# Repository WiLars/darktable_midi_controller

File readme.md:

# Midi controller for darktable

- 3D printed housing
  -  stp and stl files available  
- individually illuminated buttons depending on state of the controller using WS2812 RGB LEDs
- arduino compatible pro micro µc
  - extended input channels with 74HC165 shifht registers
  - cherry type mechanical keys
    - 8 top row for mode selction
    - 8 in bottom row for functions
  - 4 alps rotary encoders with button functions
  - powered and connected via usb
- PCB files in KiCad available
- control of darktable via midi protcol
  - fully customizable inside of darktable

## materials
| Part | amount | comment|
| -------- | ------- | ------ |
| PCB | 1 | Kicad files in this repo|
| frontcover | 1 | 3D print|
| backcover | 1 | 3D print|
| LED holder | 1 | 3D print|
| buffer | 7 | 3D print (TPU)|
| encoder knobs | 4 | 3D print|
| keycaps | 16 | 3D print|
| M3x10 screw | 7| |
| micro USB cable| 1 | |
| pro micro atmega32 | 1| arduino compatible cheap MCU|
| 74HC165 | 2|  shift registers|
| cherry type switches | 16 | accordig to taste|
| capacitor 100 nF | 2 | |
| capacitor 1 µF | 2 | or something similar |
| rotary encoder Alps EC12 | 4 | with click|
| pullup resistor | 16 | high resistance recommended > 10k Ohm |
| WS2812 RGB LED | 16 | I used a self adhesive LED strip with 60 LED/m, that way, two can be chained without soldering |
| double tape | some |  to stick the LED holder onto the PCB|
| wire | some | to connect LED strips |

## assembly
- solder al compenents to PCB
- LEDs: this is a little awkward, spacing of LEDs and switches didn't fit and I could't source any reasonably priced THT RGB LEDs
  - two LEDs from the strip are glued to the holder, position is indicated by notches
  - individual strips need to be connected with wire (3 contacts each)
  - LED holder can be glued onto the PCB with some double tape
  - then both strips (top and bottom can be connected to the PCB

- add USB cable
- add TPU buffers to the backcover
- add the case and screws
- knobs and keycaps
- flash arduino SW

## usage
*The controller must be connected during start of darktable, it can only be detected during start!*
after every start, darktable needs to notice that midi CCs are working in relative mode (default is absolute). This can be done by rotating one of the encoders left.

If darktable is running in absolute encoding, input can be reset with ctrl+alt*shift+I then again try to rotate an encoder left.

keymappsings can be imported into darktable: settings -> shortcuts -> import
 => use file *darktable_shortcut_mapping_export*

 With current arduino SW the top row of switches selects the modes, bottom row of buttons and rotary encoders can be assigned to darktable functions

 ## issues
 - darktable does not distinguish for very low "notes" for midi, therefore some buttons cannot be assigned
 - keymapping is not very complete

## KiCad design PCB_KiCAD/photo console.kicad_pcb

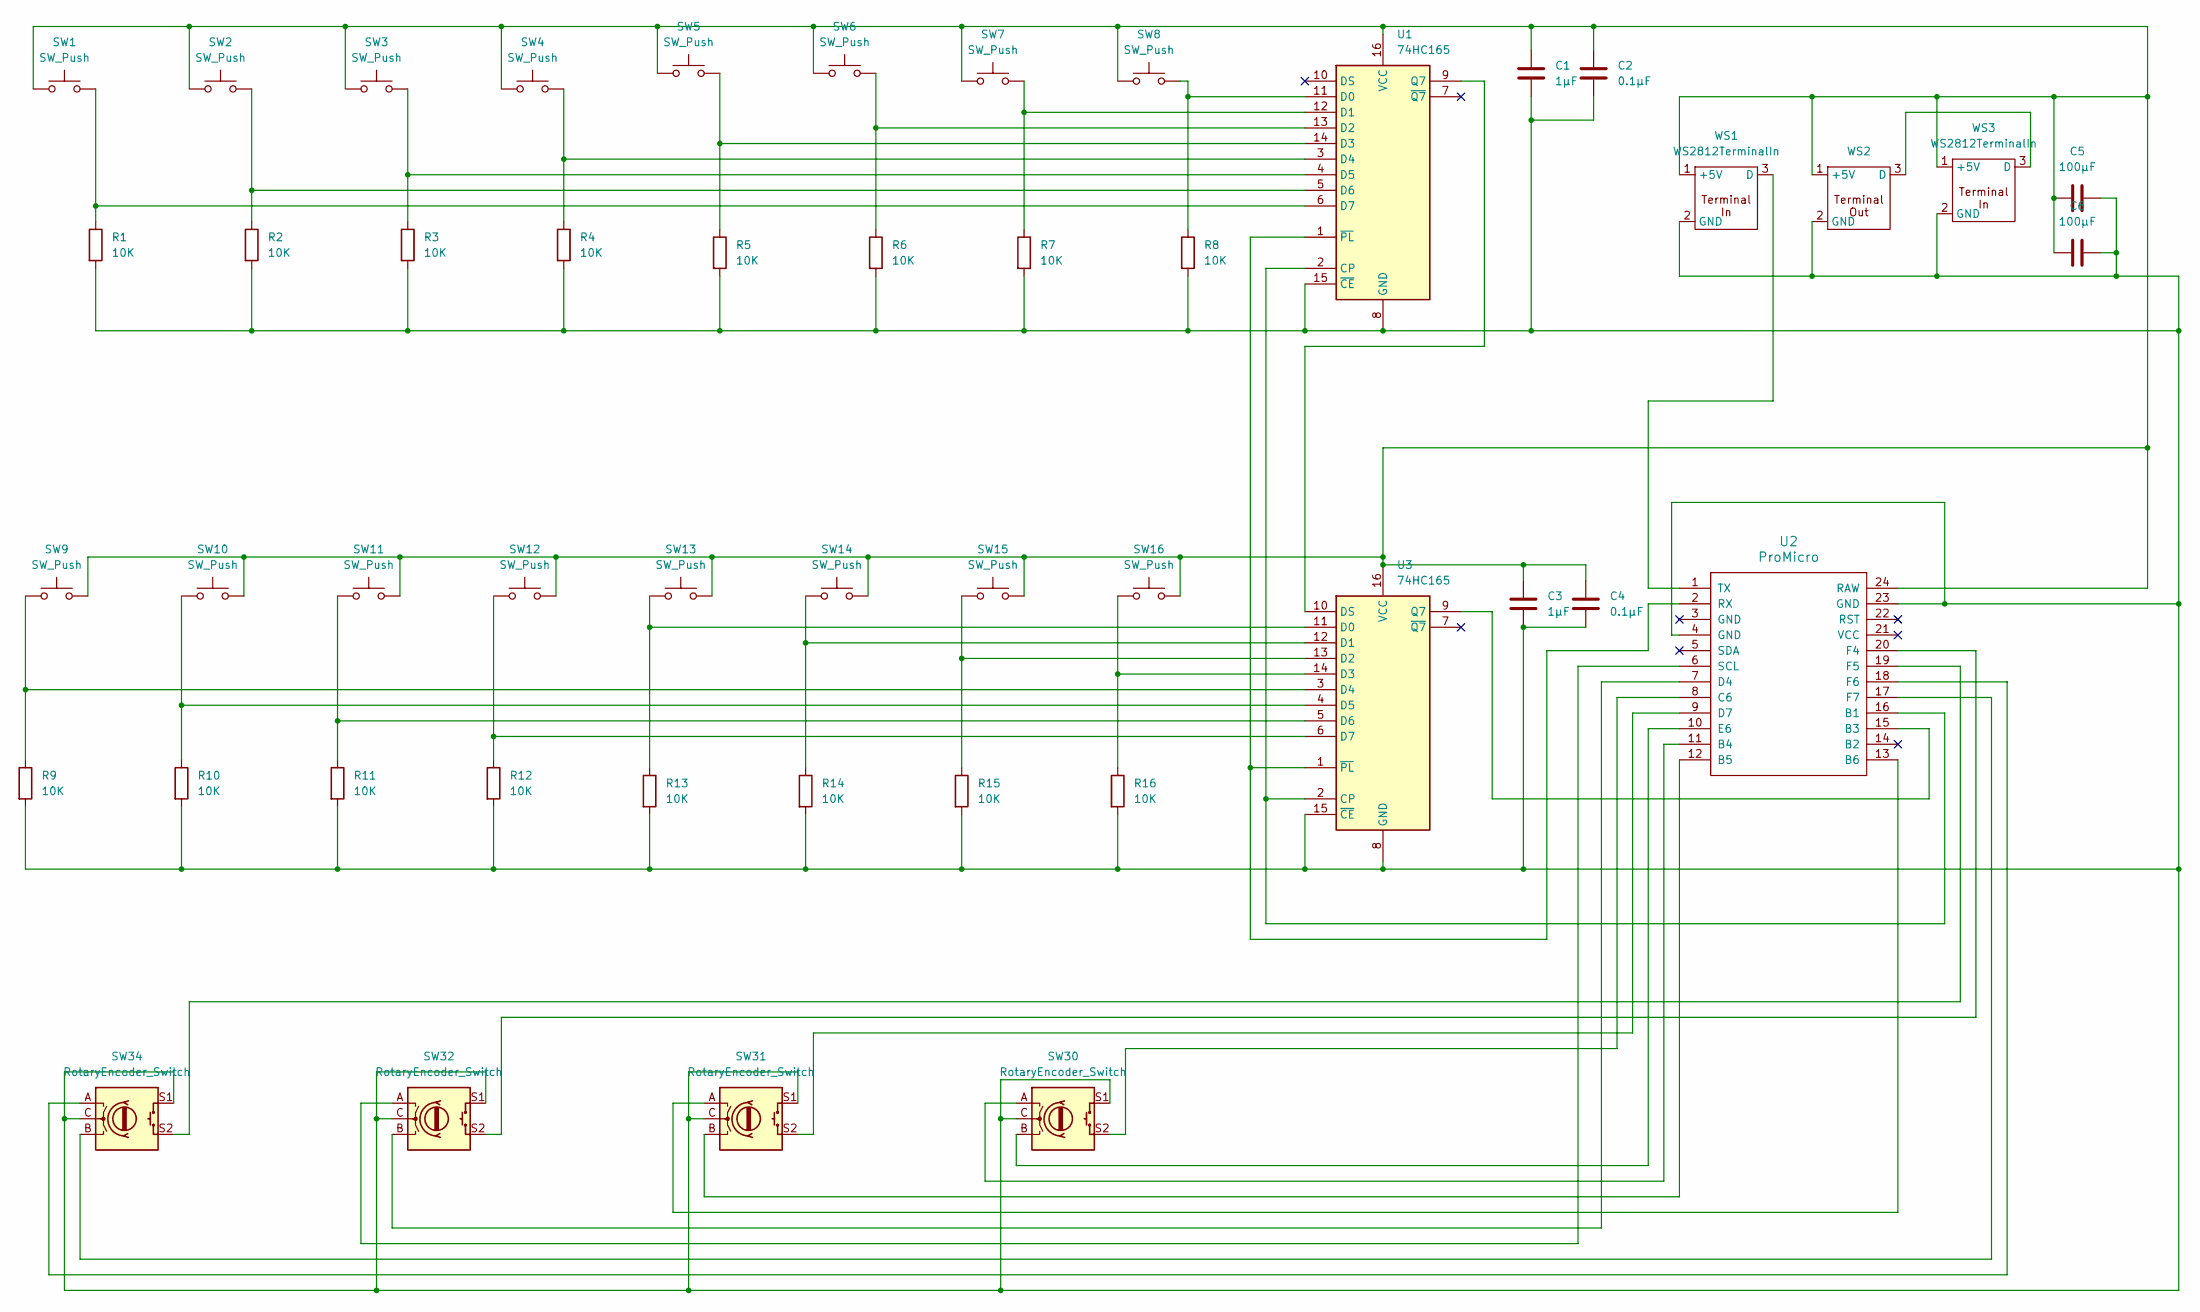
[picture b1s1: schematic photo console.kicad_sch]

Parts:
C1, C3: 1µF; C_Disc_D5.1mm_W3.2mm_P5.00mm
C2, C4: 0.1µF; C_Disc_D5.1mm_W3.2mm_P5.00mm
C5, C6: 100µF; CP_Radial_D10.0mm_P5.00mm
R1, R2, R3, R4, R5, R6, R7, R8, R9, R10, R11, R12, R13, R14, R15, R16: 10K; R_Axial_DIN0309_L9.0mm_D3.2mm_P12.70mm_Horizontal
SW1, SW2, SW3, SW4, SW5, SW6, SW7, SW8, SW9, SW10, SW11, SW12, SW13, SW14, SW15, SW16: SW_Push; SW_Cherry_MX_1.00u_PCB_center_hole
SW30, SW31, SW32, SW34: RotaryEncoder_Switch; RotaryEncoder_Alps_EC12E-Switch_Vertical_H20mm_CircularMoun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
U1, U3: 74HC165; DIP-16_W7.62mm
U2: ProMicro
WS1, WS3: WS2812TerminalIn; 3 Pin THT
WS2: 3 Pin THT

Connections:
unnamed: U1.2 (CP), U2.16 (B1), U3.2 (CP)
unnamed: R8.1, SW8.2, U1.11 (D0)
unnamed: R7.1, SW7.2, U1.12 (D1)
unnamed: R6.1, SW6.2, U1.13 (D2)
unnamed: R5.1, SW5.2, U1.14 (D3)
unnamed: R4.1, SW4.2, U1.3 (D4)
unnamed: R3.1, SW3.2, U1.4 (D5)
unnamed: R2.1, SW2.2, U1.5 (D6)
unnamed: R1.1, SW1.2, U1.6 (D7)
unnamed: C1.2, C2.2, C3.2, C4.2, C5.2, C6.2, R1.2, R2.2, R3.2, R4.2, R5.2, R6.2, R7.2, R8.2, R9.2, R10.2, R11.2, R12.2, R13.2, R14.2, R15.2, R16.2, SW30.C, SW30.S1, SW31.C, SW31.S1, SW32.C, SW32.S1, SW34.C, SW34.S1, U1.8 (GND), U1.15 (~CE), U2.4 (GND), U2.23 (GND), U3.8 (GND), U3.15 (~CE), WS1.2 (GND), WS2.2 (GND), WS3.2 (GND)
unnamed: U1.9 (Q7), U3.10 (DS)
unnamed: C1.1, C2.1, C3.1, C4.1, C5.1, C6.1, SW1.1, SW2.1, SW3.1, SW4.1, SW5.1, SW6.1, SW7.1, SW8.1, SW9.2, SW10.2, SW11.2, SW12.2, SW13.2, SW14.2, SW15.2, SW16.2, U1.16 (VCC), U2.24 (RAW), U3.16 (VCC), WS1.1 (+5V), WS2.1 (+5V), WS3.1 (+5V)
unnamed: U1.1 (~PL), U2.2 (RX), U3.1 (~PL)
unnamed: U2.15 (B3), U3.9 (Q7)
unnamed: SW30.A, U2.11 (B4)
unnamed: SW31.B, U2.12 (B5)
unnamed: SW31.A, U2.13 (B6)
unnamed: SW30.S2, U2.8 (C6)
unnamed: SW32.B, U2.7 (D4)
unnamed: SW31.S2, U2.9 (D7)
unnamed: SW30.B, U2.10 (E6)
unnamed: SW32.S2, U2.20 (F4)
unnamed: SW34.S2, U2.19 (F5)
unnamed: SW34.A, U2.18 (F6)
unnamed: SW34.B, U2.17 (F7)
unnamed: SW32.A, U2.6 (SCL)
unnamed: U2.1 (TX), WS1.3 (D)
unnamed: R13.1, SW13.1, U3.11 (D0)
unnamed: R14.1, SW14.1, U3.12 (D1)
unnamed: R15.1, SW15.1, U3.13 (D2)
unnamed: R16.1, SW16.1, U3.14 (D3)
unnamed: R9.1, SW9.1, U3.3 (D4)
unnamed: R10.1, SW10.1, U3.4 (D5)
unnamed: R11.1, SW11.1, U3.5 (D6)
unnamed: R12.1, SW12.1, U3.6 (D7)
unnamed: WS2.3 (D), WS3.3 (D)

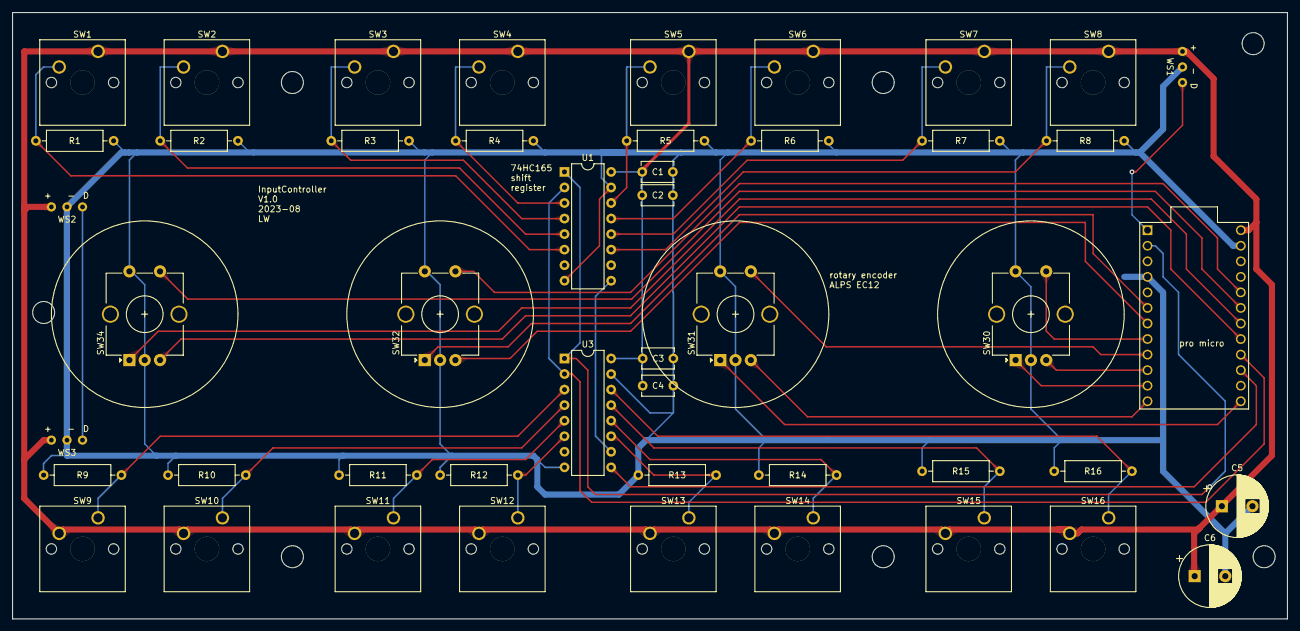
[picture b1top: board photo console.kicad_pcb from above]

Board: 2 copper layers, 208.3 x 99.1 mm, 48 parts (0 on the bottom side), 36 nets.
